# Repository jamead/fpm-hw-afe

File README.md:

# NSLS-II Fill Pattern Monitor Analog Front End

Analog front-end (AFE) board for the NSLS-II Fill Pattern Monitor.

| Item | Description |
|---|---|
| Drawing number | E-SK-2604 |
| Revision | 1 |
| Date | September 20, 2026 |
| Design software | KiCad |
| PCB | Six layers, 1.6 mm nominal thickness |

## Overview

The board accepts a broadband RF signal and produces two simultaneous 50-ohm outputs:

- **Low-gain output:** a direct, filtered monitor of the input signal.
- **High-gain output:** a filtered and amplified signal with digitally programmable attenuation.

The two outputs provide sufficient dynamic range to observe both large and small signals without changing the input connection. The programmable attenuator in the high-gain path allows its level to be adjusted for the acquisition system while reducing the risk of amplifier or ADC saturation.

## RF signal path

The signal enters the board through **J2** and first passes through **U8 (RCAT-01+)**, a fixed attenuator used to improve the input match and provide isolation. It then passes through **U4 (XLF-172H+)**, which limits the RF bandwidth before the signal reaches **U7 (RPS-2-30+)**, a two-way power splitter.

```text
J2 RF input
  -> U8 fixed attenuator
  -> U4 input filter
  -> U7 two-way splitter
       |-> J5 low-gain output
       |
       `-> U2 digital step attenuator
           -> U3 RF gain block
           -> U5 output filter
           -> J3 high-gain output
```

The RF input and both outputs are AC-coupled. Board-level RF interconnects are designed as 50-ohm transmission lines.

### Low-gain output

One output of the splitter is AC-coupled directly to **J5**. This path contains no active gain stage and provides a conditioned copy of the input for larger signals and diagnostic measurements.

### Programmable high-gain output

The second splitter output is AC-coupled to **U2 (PE43713B-Z)**, a digitally controlled RF step attenuator. U2 sets the signal level applied to **U3 (ADL5613)**, a broadband RF gain block. The amplifier supply is delivered through bias inductor **L2** and is locally bypassed by the surrounding capacitors.

After amplification, the signal passes through **U5 (XLF-172H+)** and is AC-coupled to **J3**, the high-gain output. The resulting gain depends on the fixed losses of the input network and splitter, the programmed attenuation of U2, the gain of U3, and the insertion loss of the output filter.

## Digital control

The PE43713 attenuator is controlled through **J4** using a three-wire serial interface:

- Serial data
- Serial clock
- Latch enable

The three control lines pass through 22-ohm series resistors **R5-R7**. Resistors **R1** and **R2** establish the required logic state for the attenuator's power-up/select input.

## Power supply

External DC power enters through **J1**. **U1**, a low-noise linear regulator, generates the local **+5.0 V** supply used by the RF circuitry. Bulk and high-frequency bypass capacitors are placed around the regulator and RF devices to keep the supply impedance low across the operating bandwidth.

## Connector summary

| Reference | Function |
|---|---|
| J1 | DC power input |
| J2 | RF input |
| J3 | High-gain RF output |
| J4 | Digital attenuator control |
| J5 | Low-gain RF output |

## PCB construction

The board uses the PCBWay standard six-layer stackup with solid ground reference planes on **L2** and **L5**. Top-layer RF traces are routed as 50-ohm grounded coplanar waveguide referenced to L2. Ground-stitching vias along the RF paths and around the connector transitions maintain a short return path and reduce unwanted coupling.

The RF components are placed in signal-flow order to minimize interconnect length. The four plated mounting holes are connected to ground and can bond the PCB ground to the enclosure.

Via-in-pad vias are specified to be filled with nonconductive epoxy, planarized, copper capped, and plated over in accordance with **IPC-4761 Type VII**.

## Design and fabrication notes

- The low-gain and high-gain outputs operate simultaneously.
- The high-gain output level depends on the programmed PE43713 attenuation.
- Preserve the specified 50-ohm geometry through RF pads and connector launches.
- Keep the L2 reference plane continuous beneath all top-layer RF traces.
- Fabricator changes to the stackup, dielectric materials, trace width, or coplanar gap require engineering approval.
- Review the schematic, PCB, bill of materials, and fabrication outputs together before ordering boards.

## Repository contents

The repository contains the KiCad schematic and PCB layout for the AFE. Depending on the release, it may also include project-specific symbols and footprints, the bill of materials, fabrication files, assembly information, and mechanical drawings.

## Organization

Brookhaven National Laboratory  
National Synchrotron Light Source II (NSLS-II)

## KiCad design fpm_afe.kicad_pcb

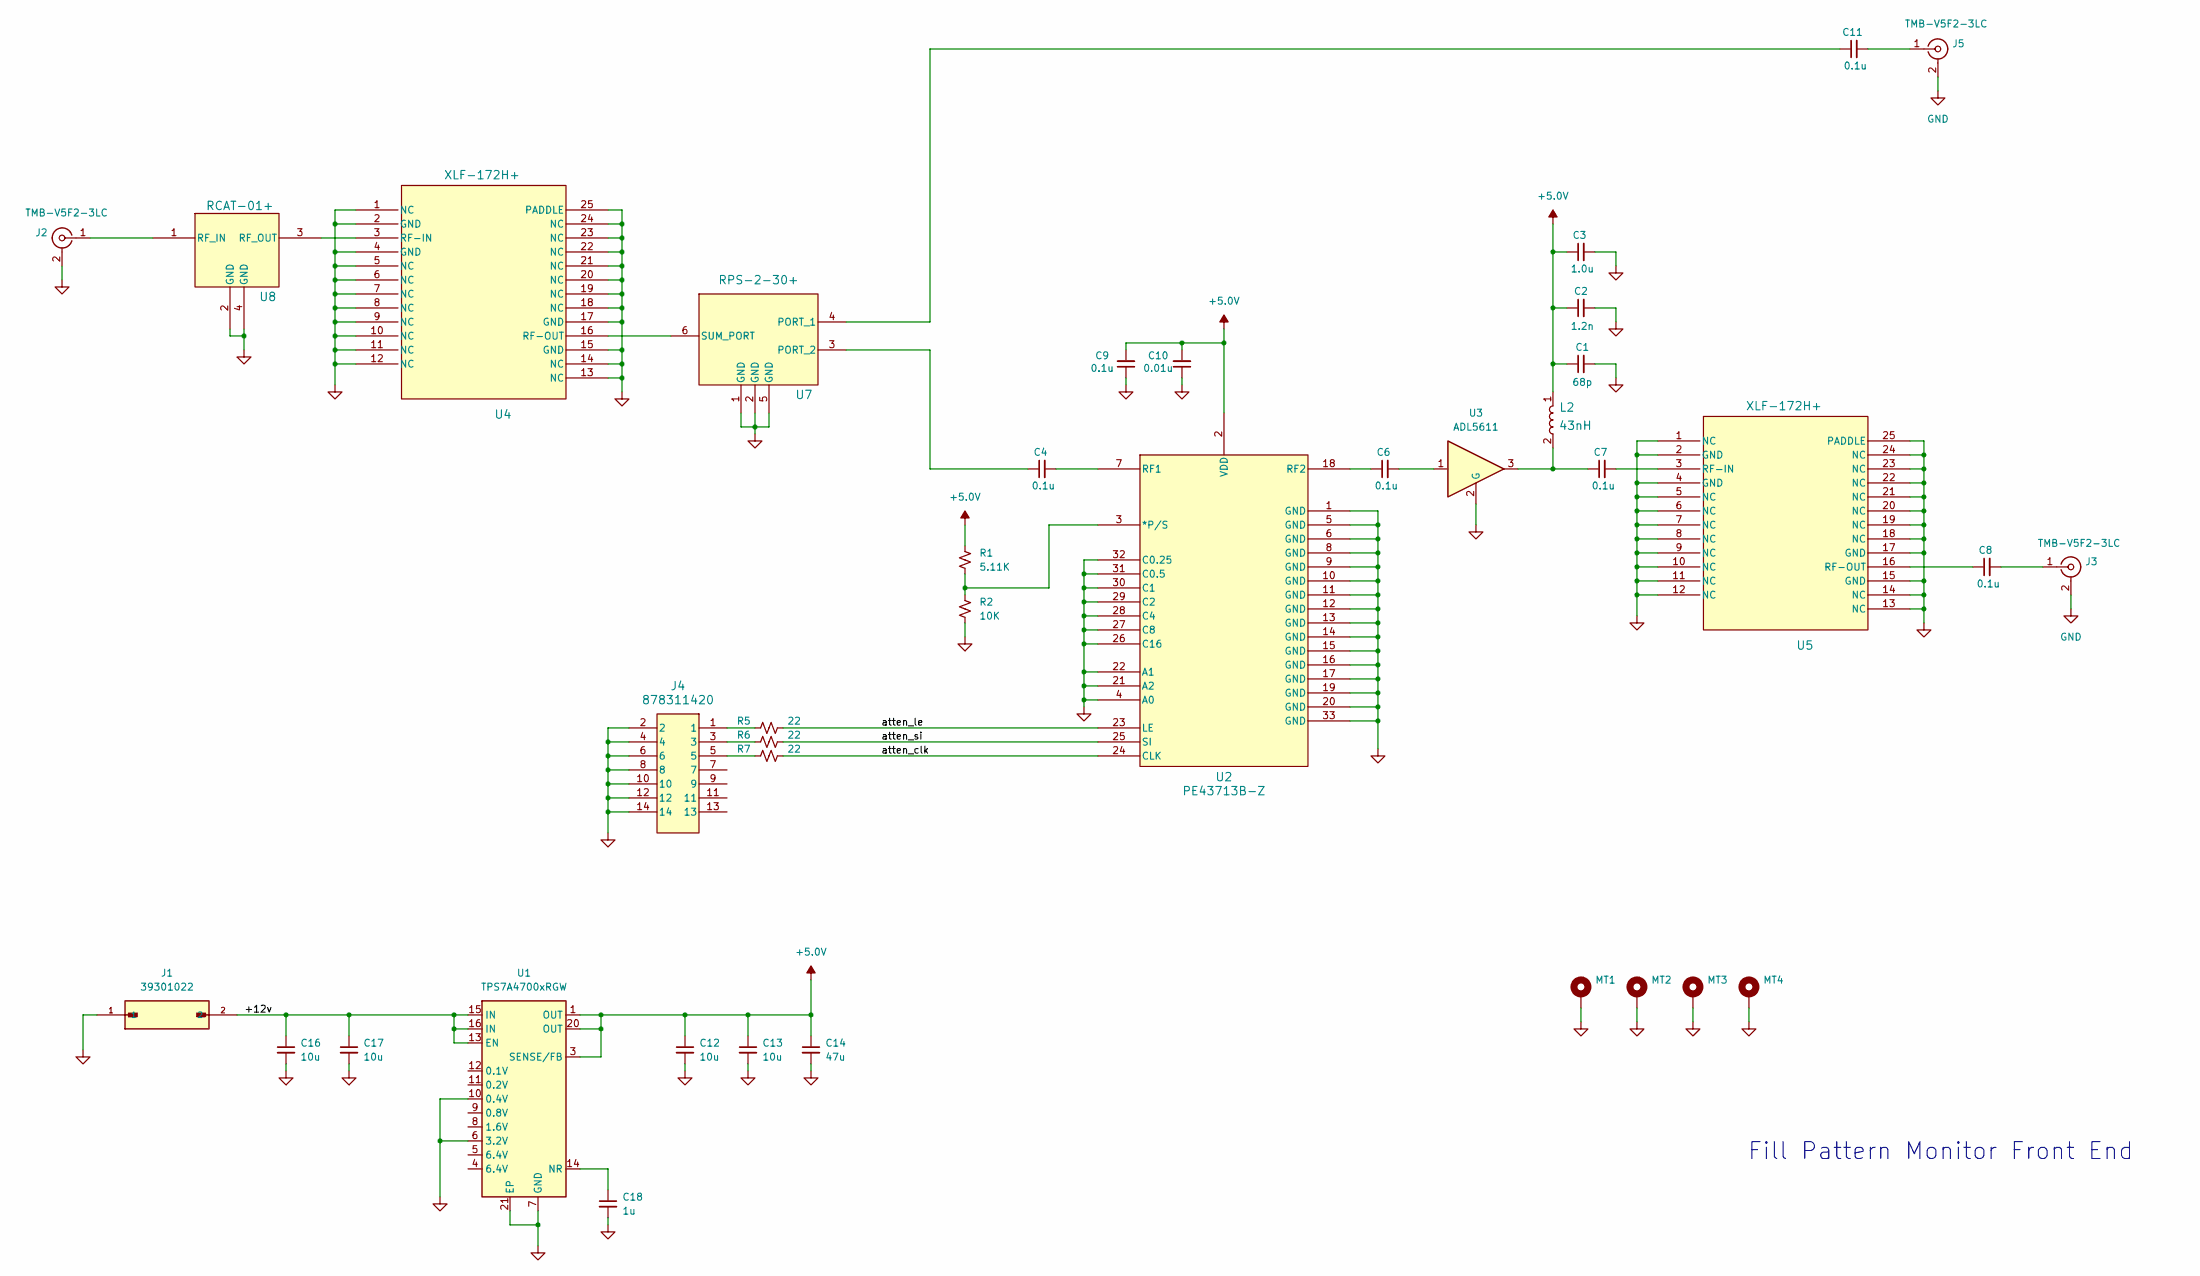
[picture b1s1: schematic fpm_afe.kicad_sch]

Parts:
C1: 68p; C_0603_1608Metric
C2: 1.2n; C_0603_1608Metric
C3: 1.0u; C_0603_1608Metric
C4, C6, C7, C8, C9, C11: 0.1u; C_0603_1608Metric
C10: 0.01u; C_0603_1608Metric
C12, C13, C16, C17: 10u; C_1206_3216Metric
C14: 47u; C_1206_3216Metric
C18: 1u; C_1206_3216Metric
J1: 39301022; MOLEX_39301022; PARTREV A
J2, J3, J5: TMB-V5F2-3LC; TMB-V5F2-3LC_PCBWay1_GCPW
J4: 878311420; CONN14_878311420_MOL; MFG_PN 0878311420
L2: 43nH; IND_0S-471XJLC_COC; MFG_PN 0603LS-471XJLC
MT1, MT2, MT3, MT4: MountingHole_Pad; MountingHole_4.3mm_M4_DIN965_Pad
R1: 5.11K; R_0603_1608Metric
R2: 10K; R_0603_1608Metric
R5, R6, R7: 22; R_0603_1608Metric
U1: TPS7A4700xRGW; Texas_RGW0020A_VQFN-20-1EP_5x5mm_P0.65mm_EP3.15x3.15mm_Ther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
U2: PE43713B-Z; QFN32_5X5_PSM
U3: ADL5611; RK_3_ADI; MFG_PN ADL5611ARKZ-R7
U4, U5: XLF-172H+; QFN24_XLF-13H&plus__MNC
U7: RPS-2-30+; TT1413_MNC
U8: RCAT-01+; RCAT_LZ1737; MFG_PN RCAT-01+

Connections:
+5.0V: C1.1, C2.1, C3.1, C9.2, C10.2, C12.1, C13.1, C14.1, L2.1, R1.1, U1.1 (OUT), U1.3 (SENSE/FB), U1.20 (OUT), U2.2 (VDD)
/+12v: C16.1, C17.1, J1.2, U1.13 (EN), U1.15 (IN), U1.16 (IN)
/atten_clk: R7.2, U2.24 (CLK)
/atten_le: R5.2, U2.23 (LE)
/atten_si: R6.2, U2.25 (SI)
GND: C1.2, C2.2, C3.2, C9.1, C10.1, C12.2, C13.2, C14.2, C16.2, C17.2, C18.2, J1.1, J2.2 (Ext), J3.2 (Ext), J4.2, J4.4, J4.6, J4.8, J4.10, J4.12, J4.14, J5.2 (Ext), MT1.1, MT2.1, MT3.1, MT4.1, R2.2, U1.6 (3.2V), U1.7 (GND), U1.10 (0.4V), U1.21 (EP), U2.1 (GND), U2.4 (A0), U2.5 (GND), U2.6 (GND), U2.8 (GND), U2.9 (GND), U2.10 (GND), U2.11 (GND), U2.12 (GND), U2.13 (GND), U2.14 (GND), U2.15 (GND), U2.16 (GND), U2.17 (GND), U2.19 (GND), U2.20 (GND), U2.21 (A2), U2.22 (A1), U2.26 (C16), U2.27 (C8), U2.28 (C4), U2.29 (C2), U2.30 (C1), U2.31 (C0.5), U2.32 (C0.25), U2.33 (GND), U3.2 (G), U4.1 (NC), U4.2 (GND), U4.4 (GND), U4.5 (NC), U4.6 (NC), U4.7 (NC), U4.8 (NC), U4.9 (NC), U4.10 (NC), U4.11 (NC), U4.12 (NC), U4.13 (NC), U4.14 (NC), U4.15 (GND), U4.17 (GND), U4.18 (NC), U4.19 (NC), U4.20 (NC), U4.21 (NC), U4.22 (NC), U4.23 (NC), U4.24 (NC), U4.25 (PADDLE), U5.1 (NC), U5.2 (GND), U5.4 (GND), U5.5 (NC), U5.6 (NC), U5.7 (NC), U5.8 (NC), U5.9 (NC), U5.10 (NC), U5.11 (NC), U5.12 (NC), U5.13 (NC), U5.14 (NC), U5.15 (GND), U5.17 (GND), U5.18 (NC), U5.19 (NC), U5.20 (NC), U5.21 (NC), U5.22 (NC), U5.23 (NC), U5.24 (NC), U5.25 (PADDLE), U7.1 (GND), U7.2 (GND), U7.5 (GND), U8.2 (GND), U8.4 (GND)
unnamed: C6.2, U3.1
unnamed: C7.1, L2.2, U3.3
unnamed: J2.1 (In), U8.1 (RF_IN)
unnamed: C8.2, J3.1 (In)
unnamed: J4.1, R5.1
unnamed: J4.3, R6.1
unnamed: J4.5, R7.1
unnamed: C11.2, J5.1 (In)
unnamed: C18.1, U1.14 (NR)
unnamed: R1.2, R2.1, U2.3 (*P/S)
unnamed: C4.2, U2.7 (RF1)
unnamed: C6.1, U2.18 (RF2)
unnamed: U4.3 (RF-IN), U8.3 (RF_OUT)
unnamed: U4.16 (RF-OUT), U7.6 (SUM_PORT)
unnamed: C7.2, U5.3 (RF-IN)
unnamed: C8.1, U5.16 (RF-OUT)
unnamed: C11.1, U7.4 (PORT_1)
unnamed: C4.1, U7.3 (PORT_2)

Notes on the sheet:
Fill Pattern Monitor Front End

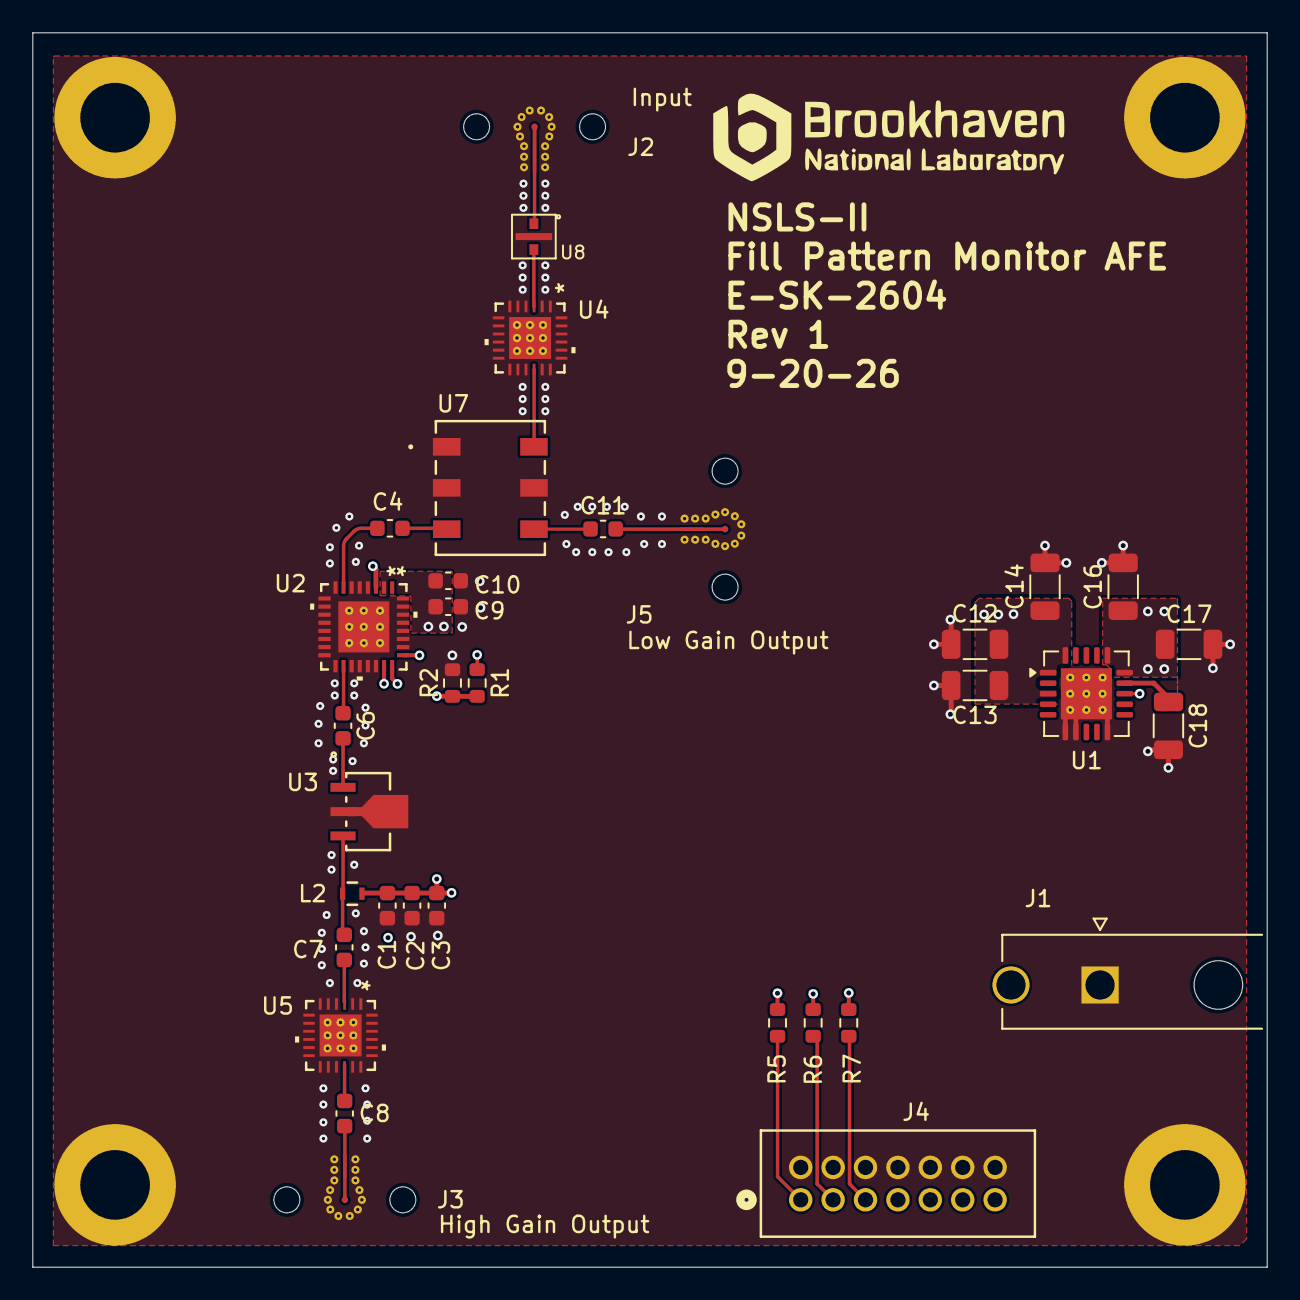
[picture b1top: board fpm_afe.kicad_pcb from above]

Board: 6 copper layers, 76.2 x 76.2 mm, 38 parts (0 on the bottom side), 24 nets.
